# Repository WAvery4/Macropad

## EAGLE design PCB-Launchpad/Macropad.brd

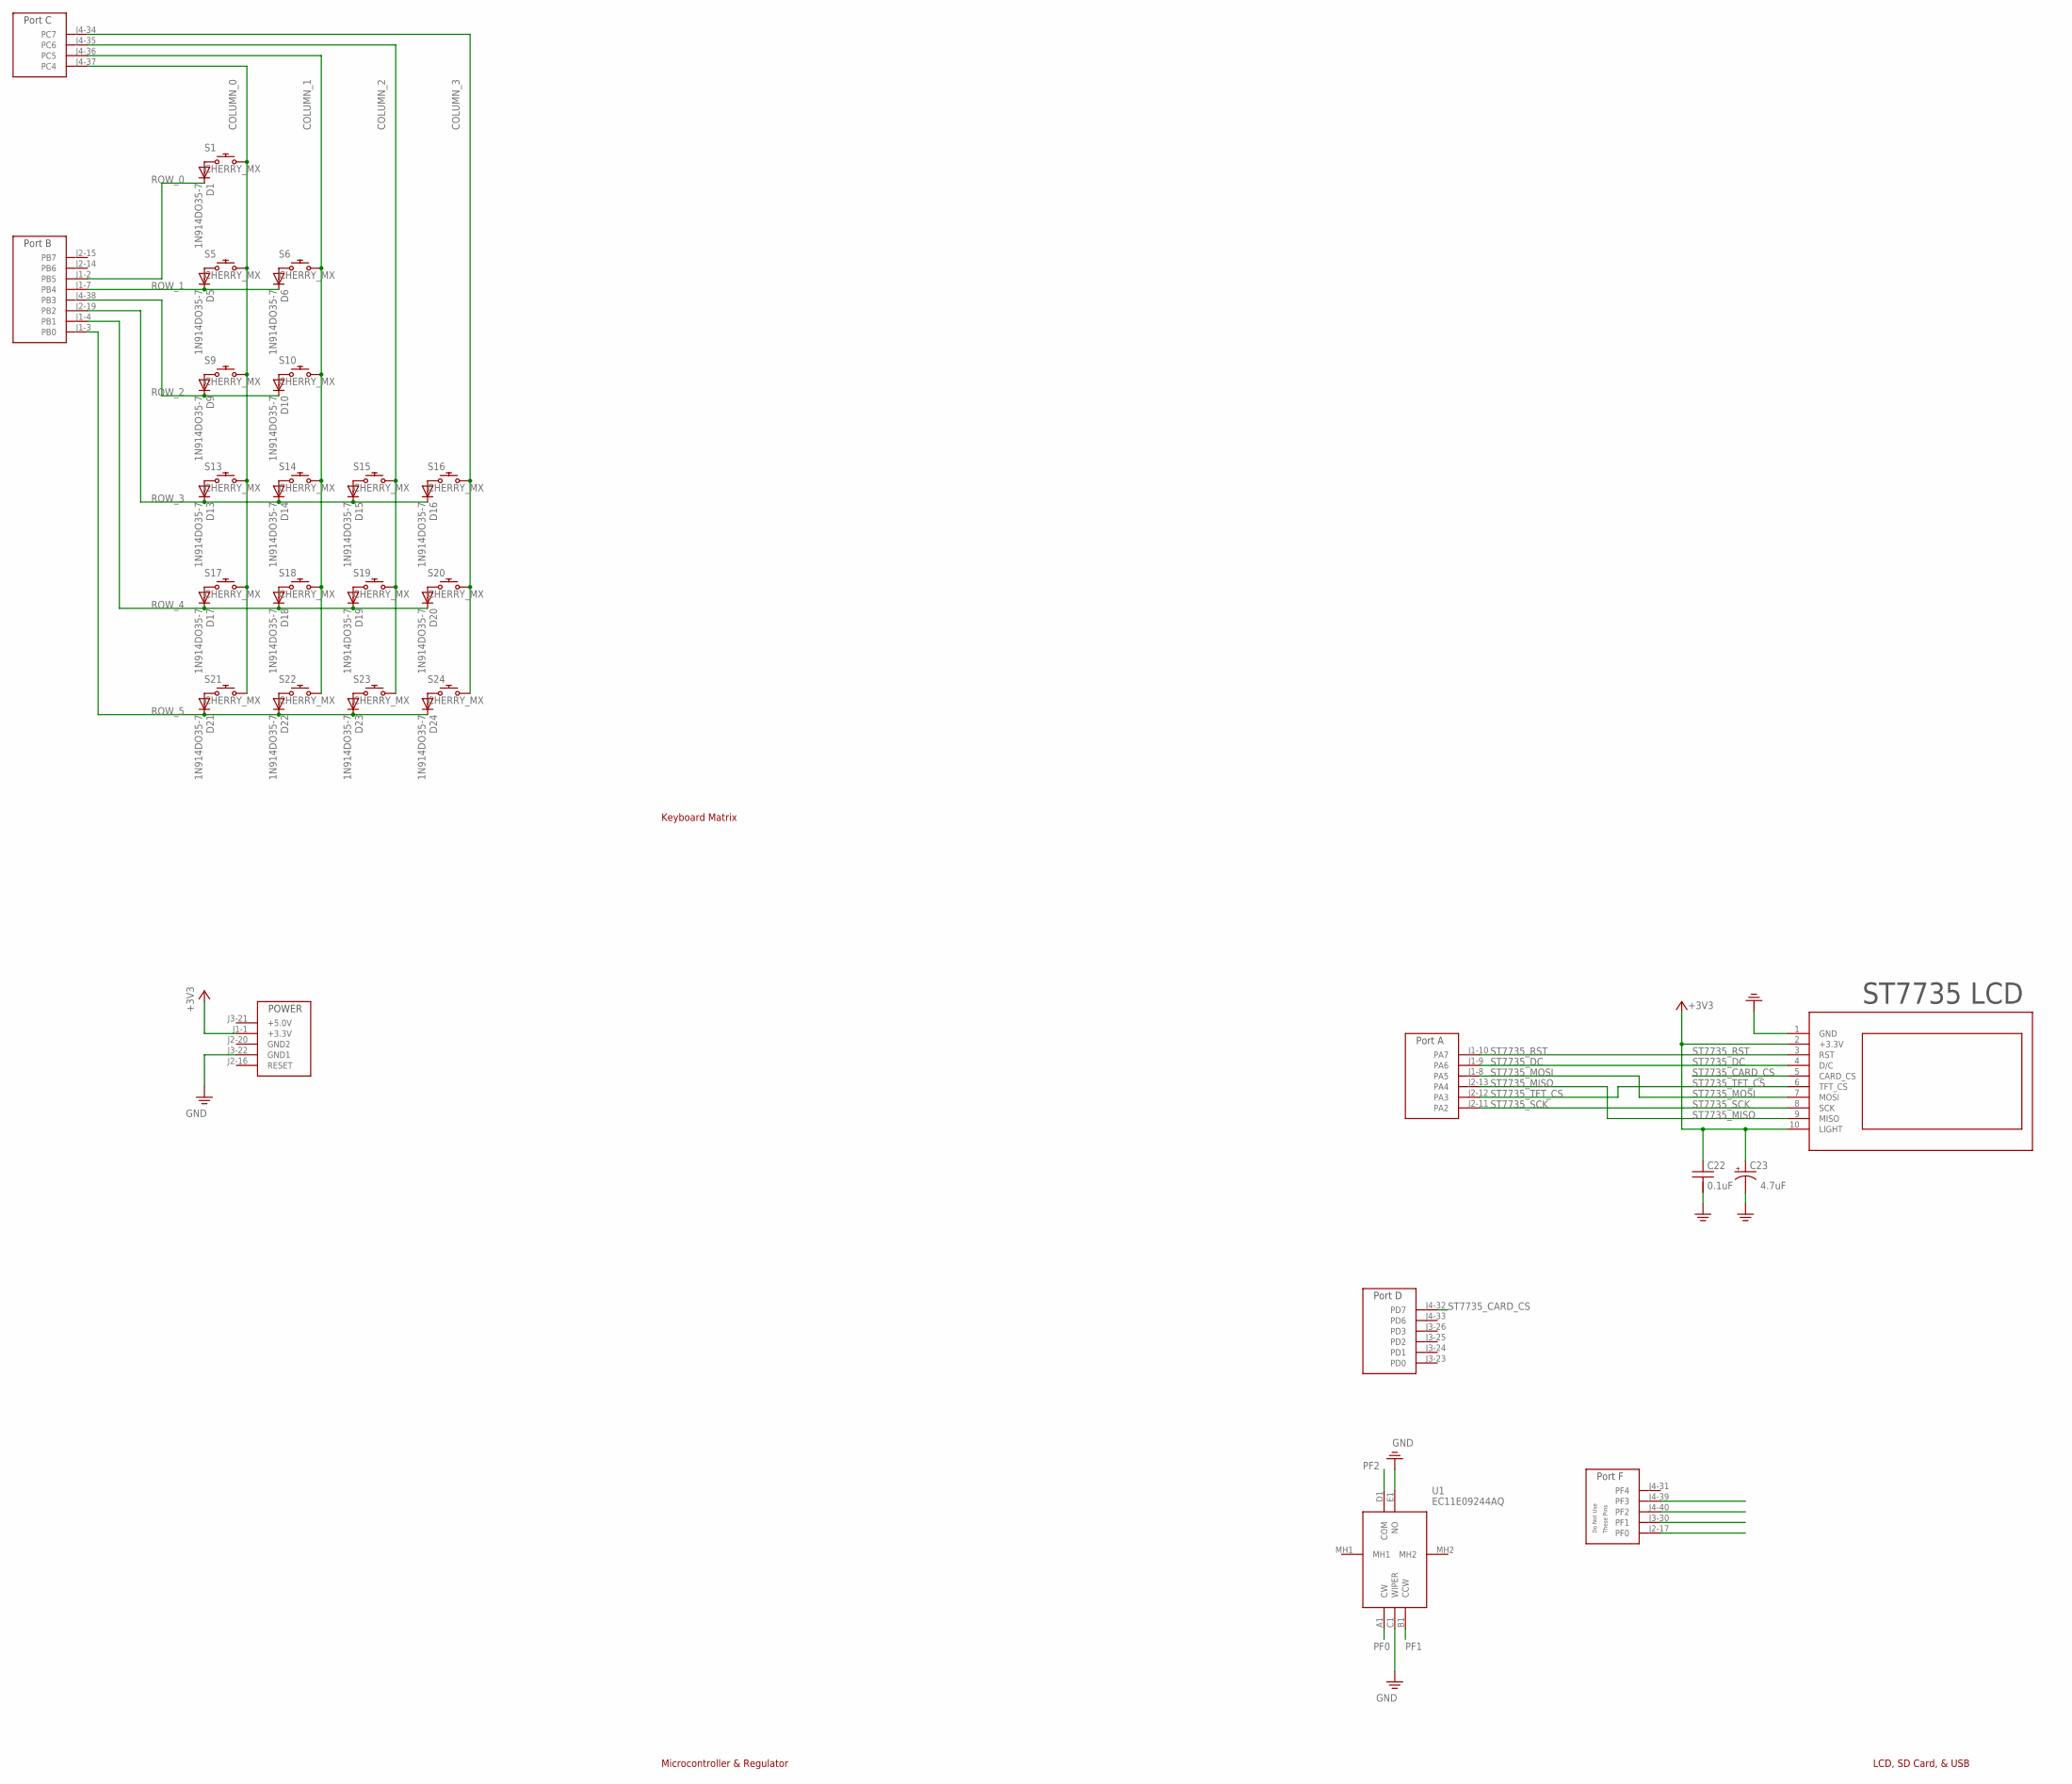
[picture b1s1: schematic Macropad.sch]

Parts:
C22: 0.1uF; CAP200MIL
C23: 4.7uF; CAP200MILPOLARIZED
D1, D5, D6, D9, D10, D13, D14, D15, D16, D17, D18, D19, D20, D21, D22, D23, D24: 1N914DO35-7; DO35-7
S1, S5, S6, S9, S10, S13, S14, S15, S16, S17, S18, S19, S20, S21, S22, S23, S24: CHERRY_MX
U1: EC11E09244AQ
U$2: TM4C_BP; TM4C_BOOSTER_PACK
U$6: ST7735

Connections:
+3V3: C22.1, C23.+, U$2.J1-1 (+3.3V), U$6.2 (+3.3V), U$6.10 (LIGHT)
COLUMN_0: S1.S2 (2), S5.S2 (2), S9.S2 (2), S13.S2 (2), S17.S2 (2), S21.S2 (2), U$2.J4-37 (PC4)
COLUMN_1: S6.S2 (2), S10.S2 (2), S14.S2 (2), S18.S2 (2), S22.S2 (2), U$2.J4-36 (PC5)
COLUMN_2: S15.S2 (2), S19.S2 (2), S23.S2 (2), U$2.J4-35 (PC6)
COLUMN_3: S16.S2 (2), S20.S2 (2), S24.S2 (2), U$2.J4-34 (PC7)
GND: C22.2, C23.-, U1.C1 (WIPER), U1.E1 (NO), U$2.J3-22 (GND1), U$6.1 (GND)
unnamed: D1.A, S1.S1 (1)
unnamed: D5.A, S5.S1 (1)
unnamed: D6.A, S6.S1 (1)
unnamed: D9.A, S9.S1 (1)
unnamed: D10.A, S10.S1 (1)
unnamed: D13.A, S13.S1 (1)
unnamed: D14.A, S14.S1 (1)
unnamed: D15.A, S15.S1 (1)
unnamed: D16.A, S16.S1 (1)
unnamed: D17.A, S17.S1 (1)
unnamed: D18.A, S18.S1 (1)
unnamed: D19.A, S19.S1 (1)
unnamed: D20.A, S20.S1 (1)
unnamed: D21.A, S21.S1 (1)
unnamed: D22.A, S22.S1 (1)
unnamed: D23.A, S23.S1 (1)
unnamed: D24.A, S24.S1 (1)
PF0: U1.A1 (CW), U$2.J2-17 (PF0)
PF1: U1.B1 (CCW), U$2.J3-30 (PF1)
PF2: U1.D1 (COM), U$2.J4-40 (PF2)
PF3: U$2.J4-39 (PF3)
ROW_0: D1.C, U$2.J1-2 (PB5)
ROW_1: D5.C, D6.C, U$2.J1-7 (PB4)
ROW_2: D9.C, D10.C, U$2.J4-38 (PB3)
ROW_3: D13.C, D14.C, D15.C, D16.C, U$2.J2-19 (PB2)
ROW_4: D17.C, D18.C, D19.C, D20.C, U$2.J1-4 (PB1)
ROW_5: D21.C, D22.C, D23.C, D24.C, U$2.J1-3 (PB0)
ST7735_CARD_CS: U$2.J4-32 (PD7), U$6.5 (CARD_CS)
ST7735_DC: U$2.J1-9 (PA6), U$6.4 (D/C)
ST7735_MISO: U$2.J2-13 (PA4), U$6.9 (MISO)
ST7735_MOSI: U$2.J1-8 (PA5), U$6.7 (MOSI)
ST7735_RST: U$2.J1-10 (PA7), U$6.3 (RST)
ST7735_SCK: U$2.J2-11 (PA2), U$6.8 (SCK)
ST7735_TFT_CS: U$2.J2-12 (PA3), U$6.6 (TFT_CS)

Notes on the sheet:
ST7735 LCD
Keyboard Matrix
Microcontroller & Regulator
LCD, SD Card, & USB

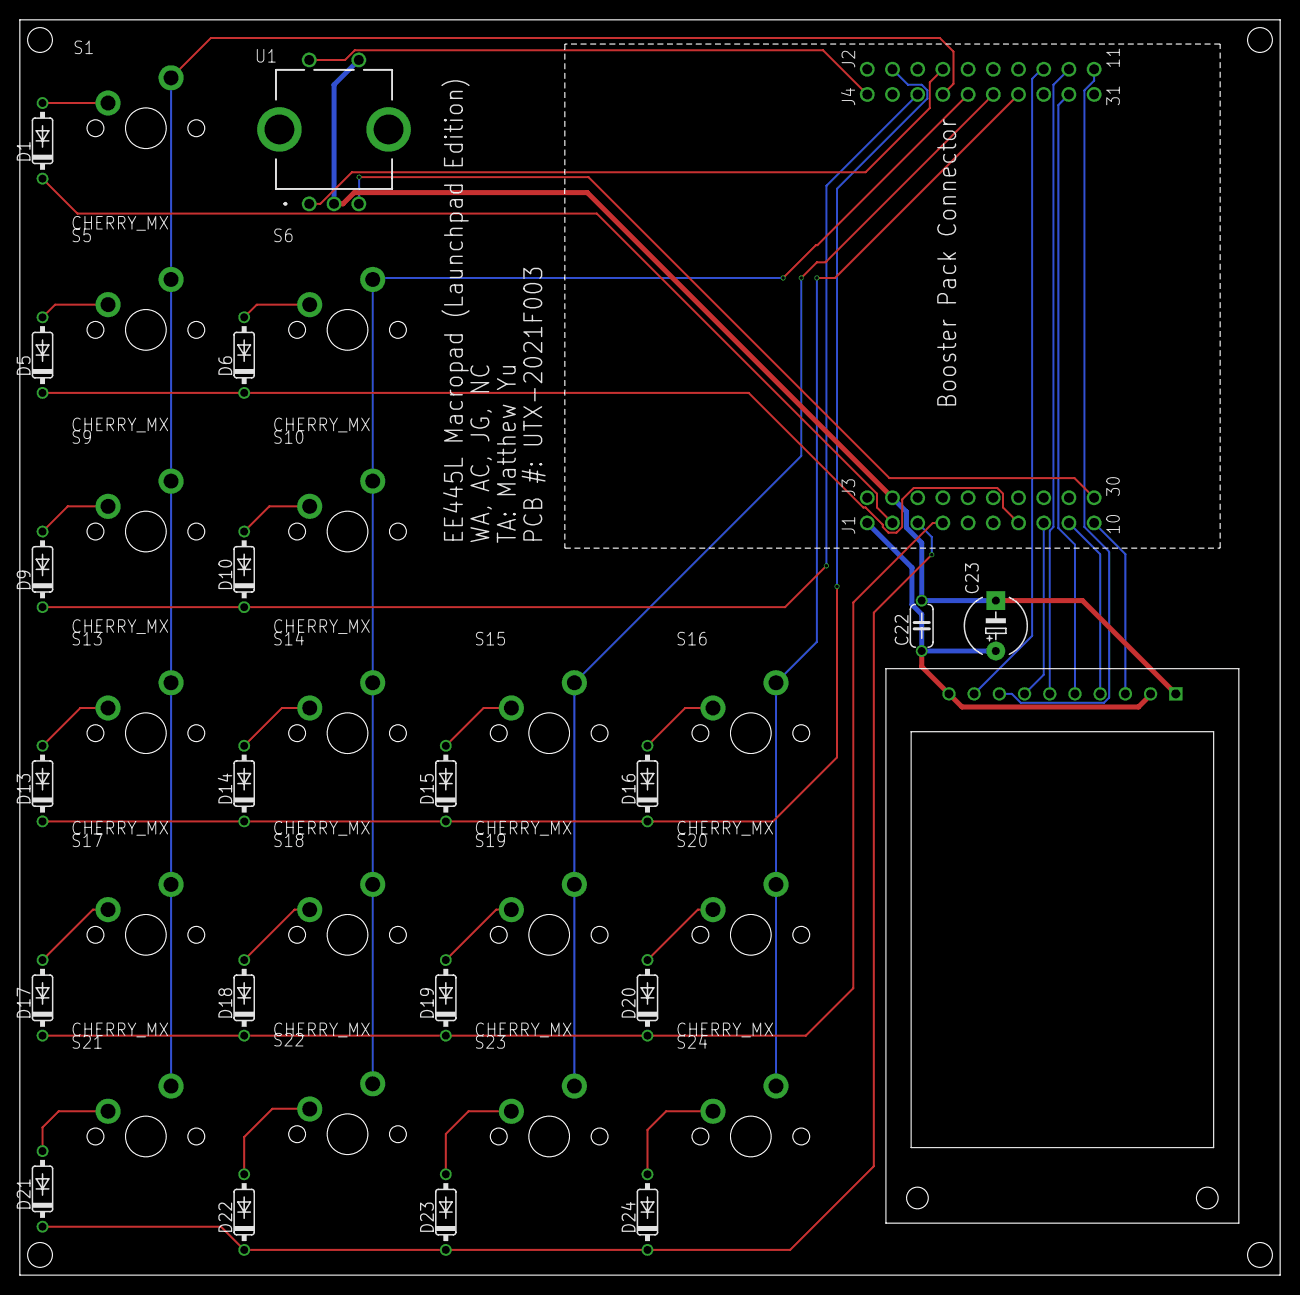
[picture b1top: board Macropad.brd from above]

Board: 2 copper layers, 127.0 x 126.5 mm, 39 parts (0 on the bottom side), 39 nets.

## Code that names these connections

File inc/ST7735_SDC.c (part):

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// Runs on LM4F120/TM4C123
// Low level drivers for the ST7735 160x128 LCD based off of
// the file described above.  Further modified for simultaneous
// use of the SD card (CS on PD7) and ST7735 LCD (CS on PA3).
//    16-bit color, 128 wide by 160 high LCD
// Daniel Valvano
// April 1, 2016
// Augmented 7/17/2014 to have a simple graphics facility
// Tested with LaunchPadDLL.dll simulator 9/2/2014
// added PB0 as a choice for SDC CS


/* This example accompanies the book
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// **********ST7735 TFT and SDC*******************
// ST7735
// Backlight (pin 10) connected to +3.3 V
// MISO (pin 9) connected to PA4 (SSI0Rx)
// SCK (pin 8) connected to PA2 (SSI0Clk)
// MOSI (pin 7) connected to PA5 (SSI0Tx)
// TFT_CS (pin 6) connected to PA3 (GPIO/SSI0Fss)
// CARD_CS (pin 5) connected to PD7 or PB0 (GPIO)
// Data/Command (pin 4) connected to PA6 (GPIO), high for data, low for command
// RESET (pin 3) connected to PA7 (GPIO)
// VCC (pin 2) connected to +3.3 V
// Gnd (pin 1) connected to ground

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// Silkscreen Label (SDC side up; LCD side down) - Connection
// VCC  - +3.3 V
// GND  - Ground
// !SCL - PA2 Sclk SPI clock from microcontroller to TFT or SDC
// !SDA - PA5 MOSI SPI data from microcontroller to TFT or SDC
// DC   - PA6 TFT data/command
// RES  - PA7 TFT reset
// CS   - PA3 TFT_CS, active low to enable TFT
// *CS  - PD7 or PB0 SDC_CS, active low to enable SDC
// MISO - PA4 MISO SPI data from SDC to microcontroller
// SDA   (NC) I2C data for ADXL345 accelerometer
// SCL   (NC) I2C clock for ADXL345 accelerometer
// SDO   (NC) I2C alternate address for ADXL345 accelerometer
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#define SDC_CS_PB0 0
#define SDC_CS_PD7 1

// SDC CS is PD7 or PB0 , TFT CS is PA3
// to change CS to another GPIO, change SDC_CS and CS_Init
// **********ST7735 TFT and SDC*******************
// ST7735
// 1  ground
// 2  Vcc +3.3V
// 3  PA7 TFT reset
// 4  PA6 TFT data/command
// 5  PD7/PB0 SDC_CS, active low to enable SDC
// 6  PA3 TFT_CS, active low to enable TFT
// 7  PA5 MOSI SPI data from microcontroller to TFT or SDC
// 8  PA2 Sclk SPI clock from microcontroller to TFT or SDC
// 9  PA4 MOSO SPI data from SDC to microcontroller
// 10 Light, backlight connected to +3.3 V

// **********wide.hk ST7735R*******************
// Silkscreen Label (SDC side up; LCD side down) - Connection
// VCC  - +3.3 V
// GND  - Ground
// !SCL - PA2 Sclk SPI clock from microcontroller to TFT or SDC
// !SDA - PA5 MOSI SPI data from microcontroller to TFT or SDC
// DC   - PA6 TFT data/command
// RES  - PA7 TFT reset
// CS   - PA3 TFT_CS, active low to enable TFT
// *CS  - PD7/PB0 SDC_CS, active low to enable SDC
// MISO - PA4 MISO SPI data from SDC to microcontroller
// SDA   (NC) I2C data for ADXL345 accelerometer
// SCL   (NC) I2C clock for ADXL345 accelerometer
// SDO   (NC) I2C alternate address for ADXL345 accelerometer
// Backlight + - Light, backlight connected to +3.3 V

#define TFT_CS           (*((volatile uint32_t *)0x40004020))
#define TFT_CS_LOW       0 // CS controlled by software PA3
#define TFT_CS_HIGH      0x08
#if SDC_CS_PD7
// PD7 output used for SDC CS
#define SDC_CS           (*((volatile uint32_t *)0x40007200))
#define SDC_CS_LOW       0           // CS controlled by software
#define SDC_CS_HIGH      0x80
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  SYSCTL_RCGCGPIO_R |= 0x08;            // activate clock for Port D
  while((SYSCTL_PRGPIO_R&0x08) == 0){}; // allow time for clock to stabilize
  GPIO_PORTD_LOCK_R = 0x4C4F434B;       // unlock GPIO Port D
  GPIO_PORTD_CR_R = 0xFF;               // allow changes to PD7-0
  // only PD7 needs to be unlocked, other bits can't be locked
  GPIO_PORTD_DIR_R |= 0x80;             // make PD7 out
  GPIO_PORTD_AFSEL_R &= ~0x80;          // disable alt funct on PD7
  GPIO_PORTD_DR4R_R |= 0x80;            // 4mA drive on outputs
  GPIO_PORTD_PUR_R |= 0x80;             // enable weak pullup on PD7
  GPIO_PORTD_DEN_R |= 0x80;             // enable digital I/O on PD7
                                        // configure PD7 as GPIO
  GPIO_PORTD_PCTL_R = (GPIO_PORTD_PCTL_R&0x0FFFFFFF)+0x00000000;
  GPIO_PORTD_AMSEL_R &= ~0x80;          // disable analog functionality on PD7
  SDC_CS = SDC_CS_HIGH;
}
#endif
// PB0 output used for SDC CS
#if SDC_CS_PB0
#define SDC_CS           (*((volatile uint32_t *)0x40005004))
#define SDC_CS_LOW       0           // CS controlled by software
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void SDC_CS_Init(void){
  SYSCTL_RCGCGPIO_R |= 0x02;            // activate clock for Port B
  while((SYSCTL_PRGPIO_R&0x02) == 0){}; // allow time for clock to stabilize
  GPIO_PORTB_DIR_R |= 0x01;             // make PB0 out
  GPIO_PORTB_AFSEL_R &= ~0x01;          // disable alt funct on PB0
  GPIO_PORTB_DR4R_R |= 0x01;            // 4mA drive on outputs
  GPIO_PORTB_PUR_R |= 0x01;             // enable weak pullup on PB0
  GPIO_PORTB_DEN_R |= 0x01;             // enable digital I/O on PB0
                                        // configure PB0 as GPIO
  GPIO_PORTB_PCTL_R = (GPIO_PORTB_PCTL_R&0xFFFFFFF0)+0x00000000;
  GPIO_PORTB_AMSEL_R &= ~0x01;          // disable analog functionality on PB0
  SDC_CS = SDC_CS_HIGH;
}
#endif
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
  // toggle RST low to reset; CS low so it'll listen to us
  // SSI0Fss is used as GPIO
  GPIO_PORTA_DIR_R |= 0xC8;             // make PA3,6,7 out
  GPIO_PORTA_AFSEL_R &= ~0xC8;          // disable alt funct on PA3,6,7
  GPIO_PORTA_DEN_R |= 0xC8;             // enable digital I/O on PA3,6,7
                                        // configure PA3,6,7 as GPIO
  GPIO_PORTA_PCTL_R = (GPIO_PORTA_PCTL_R&0x00FF0FFF)+0x00000000;
  GPIO_PORTA_AMSEL_R &= ~0xC8;          // disable analog functionality on PA3,6,7
  TFT_CS = TFT_CS_LOW;
  RESET = RESET_HIGH;
  Delay1ms(500);
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  Delay1ms(500);

  // initialize SSI0
  GPIO_PORTA_AFSEL_R |= 0x34;           // enable alt funct on PA2,4,5
  GPIO_PORTA_PUR_R |= 0x3C;             // enable weak pullup on PA2,3,4,5
  GPIO_PORTA_DEN_R |= 0x34;             // enable digital I/O on PA2,4,5
                                        // configure PA2,4,5 as SSI
  GPIO_PORTA_PCTL_R = (GPIO_PORTA_PCTL_R&0xFF00F0FF)+0x00220200;
  GPIO_PORTA_AMSEL_R &= ~0x34;          // disable analog functionality on PA2,4,5
  SDC_CS_Init();                        // SDC CS on PB0 or PD7
  SDC_CS = SDC_CS_HIGH;
  SSI0_CR1_R &= ~SSI_CR1_SSE;           // disable SSI
  SSI0_CR1_R &= ~SSI_CR1_MS;            // master mode
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
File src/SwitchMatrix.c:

#define PORT_B_PRIORITY 2
#define TIMER0A_PRIORITY 3

#include <stdbool.h>
#include <stdint.h>
#include "../inc/tm4c123gh6pm.h"
#include "../inc/Timer2A.h"
#include "Macro.h"
#include "SwitchMatrix.h"

long StartCritical(void);
void EndCritical(long sr);

static uint8_t ColumnIndex;

/**
 * Arm interrupts for PB5-PB0.
 */
static void ArmPortB(void)
{
    GPIO_PORTB_ICR_R = 0x3F;                                         // Clear flags
    GPIO_PORTB_IM_R |= 0x3F;                                         // Arm interrupts
    NVIC_PRI0_R = (NVIC_PRI0_R & ~0xE000) | (PORT_B_PRIORITY << 13); // Set priority (bits 15-13)
    NVIC_EN0_R = 1 << 1;                                             // Enable IRQ 1 in NVIC
}

/**
 * Arm Timer0A for debouncing.
 * 
 * @param period the duration of the timer
 */
static void Timer0A_Arm(uint32_t period)
{
    SYSCTL_RCGCTIMER_R |= 0x01;                                          // 0) activate Timer0
    TIMER0_CTL_R &= ~0x01;                                               // 1) disable Timer0A during setup
    TIMER0_CFG_R = 0x00;                                                 // 2) configure for 32-bit timer mode
    TIMER0_TAMR_R = 0x01;                                                // 3) 1-shot mode
    TIMER0_TAILR_R = period - 1;                                         // 4) reload value
    TIMER0_TAPR_R = 0;                                                   // 5) 12.5ns Timer0A
    TIMER0_ICR_R = 0x01;                                                 // 6) clear Timer0A timeout flag
    TIMER0_IMR_R |= 0x01;                                                // 7) arm timeout interrupt
    NVIC_PRI4_R = (NVIC_PRI4_R & 0x00FFFFFF) | (TIMER0A_PRIORITY << 29); // 8) set priority
    NVIC_EN0_R = 1 << 19;                                                // 9) enable IRQ 19 in NVIC
    TIMER0_CTL_R |= 0x01;                                                // 10) enable Timer0A
}

/**
 * Initialize PB5-PB0 as row input.
 */
static void InitRows(void)
{
    SYSCTL_RCGCGPIO_R |= 0x02; // Activate clock for Port B

    while ((SYSCTL_PRGPIO_R & 0x02) == 0)
    {
        // Wait for activation
    }

    GPIO_PORTB_DIR_R &= ~0x3F;        // Set as input
    GPIO_PORTB_AFSEL_R &= ~0x3f;      // Disable alternate function
    GPIO_PORTB_DEN_R |= 0x3F;         // Enable digital I/O
    GPIO_PORTB_PCTL_R &= ~0x00FFFFFF; // Configure as GPIO
    GPIO_PORTB_AMSEL_R &= ~0x3F;      // Disable analog functionality
    GPIO_PORTB_PDR_R |= 0x3F;         // Enable pull-down resistors
    GPIO_PORTB_IS_R &= ~0x3F;         // Set as edge-sensitive
    GPIO_PORTB_IBE_R |= 0x3F;         // Set trigger to both edges

    ArmPortB();
}

/**
 * Initialize PC7-PC4 as column output.
 */
static void InitColumns(void)
{
    ColumnIndex = 0;
    SYSCTL_RCGCGPIO_R |= 0x04; // Activate clock for Port C

    while ((SYSCTL_PRGPIO_R & 0x04) == 0)
    {
        // Wait for activation
    }

    GPIO_PORTC_LOCK_R = 0x4C4F434B;   // Unlock GPIO for port C
    GPIO_PORTC_DIR_R |= 0xF0;         // Set as output
    GPIO_PORTC_AFSEL_R &= ~0xF0;      // Disable alternate function
    GPIO_PORTC_DEN_R |= 0xF0;         // Enable digital I/O
    GPIO_PORTC_PCTL_R &= ~0xFFFF0000; // Configure as GPIO
    GPIO_PORTC_AMSEL_R &= ~0xF0;      // Disable analog functionality

    SwitchMatrix_CycleColumnOutput();
}

/**
 * Handle port B interaction.
 */
void GPIOPortB_Handler(void)
{
    GPIO_PORTB_IM_R &= ~0x3F; // Disarm interrupts
    uint32_t triggeredPortB = GPIO_PORTB_RIS_R & 0x3F;

    for (uint8_t i = 0; i < ROW_COUNT; i++)
    {
        if (triggeredPortB >> i == 1)
        {
            // Handle switch press
            Macro selectedMacro = Macro_Keybindings[ROW_COUNT-1-i][ColumnIndex];

            Macro_Execute(selectedMacro, false);
        }
    }

    Timer0A_Arm(8000000);
}

/**
 * Handle re-arming port B.
 */
void Timer0A_Handler(void)
{
    TIMER0_ICR_R = TIMER_ICR_TATOCINT; // acknowledge timer0A timeout

    ArmPortB();
}

void SwitchMatrix_Init(void)
{
    Timer2A_Init(SwitchMatrix_CycleColumnOutput, 800000, 1);
    InitRows();
    InitColumns();
}

void SwitchMatrix_CycleColumnOutput(void)
{
    ColumnIndex = (ColumnIndex + 1) % COLUMN_COUNT;
    PC7654 = 1 << (ColumnIndex + COLUMN_COUNT);
}

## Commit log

2021-10-17 Initial PCB design
2021-10-17 Added JTAG connection
2021-10-19 Started pcb layout
2021-10-19 Added rotary encoder
2021-10-21 Finished first draft of PCB layout
2021-10-25 Added drill holes for mounting
2021-10-26 Updated power lines
2021-10-26 Add .gitignore
2021-10-26 Add helper files
2021-10-26 Create starter Keil project
2021-10-26 updated some routing
2021-10-27 Added Matthew's urgent updates
2021-10-27 Fixed ground loop
2021-10-27 Changed TVS part
2021-10-27 Added not urgent but recommended updates
2021-10-27 Added PCB #
2021-10-27 pcb updates
2021-10-27 Final touchups with TA
2021-10-27 Reduced board to 4.98x5 inches
2021-10-28 Evenly spaced the keys
2021-10-28 Add starter files for switch matrix and macros
2021-10-28 got started with rotary switch driver code prep
2021-10-28 fixed wrong gpio direction for port F
2021-10-28 Refactor column cycle logic
2021-10-28 Fix Timer0A for switch matrix and Timer1A for rotary switch
2021-10-28 Refactor switch matrix to use bit-banding for port C
2021-10-29 Added FAT drivers and tests
2021-10-30 Updated Macro.c to read from mac.txt from a micro SD card
    Macro_Init() reads the contents of mac.txt, which is contained in a micro SD card. The initializer also outputs the names of each macro in a 6x4 grid on the ST7735. Additionally ST7735.c has been upd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
2021-10-30 Updated Macro.c to correctly save name strings
2021-10-31 Fix logic for port B handler
2021-10-31 Add USB drivers and keyboard example
2021-10-31 Updated startup.s
2021-11-01 Revert "Updated startup.s"
    This reverts commit 13a5ae0fa9e6a3aee5ad60c3c7faf38ad36caae4.
2021-11-01 Fixed startup
2021-11-01 Change TivaWare library to relative paths
2021-11-01 Update .gitignore to include .lib files from source
2021-11-01 Update startup.s and fix switch matrix buttons
2021-11-02 Updated startup.s to fix keyboard example
2021-11-23 Fix rotary knob rotation and add volume HID modifiers
2021-11-26 implementing usb interface with consumer device
2021-11-26 Updated HID report descriptor
2021-11-26 padding for media keys
2021-11-28 started on figuring out multikeys, will need to look into potential media keys too
2021-11-29 separate normal and media key calls
2021-11-29 split media and normal key with a bool instead in macro execution
2021-11-30 Fixed keyboard misinput
2021-11-30 Added modifier functionality
2021-11-30 Fixed rotary switch
2021-12-01 Fixed modifiers
2021-12-02 Added PCB-Launchpad schematic

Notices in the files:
inc/ST7735_SDC.c:
MIT license, all text above must be included in any redistribution
"Embedded Systems: Real Time Interfacing to ARM Cortex M Microcontrollers",
ISBN: 978-1463590154, Jonathan Valvano, copyright (c) 2016
Copyright 2016 by Jonathan W. Valvano, valvano@mail.utexas.edu
